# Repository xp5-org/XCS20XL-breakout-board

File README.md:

Unfinished test breakout board for the Spartan-XL XCS20XL-4TQ144C 

need to sort out the power connector and programming port layout but otherwise is mostly complete

footprint from here : https://web.archive.org/web/20240531214501/https://app.ultralibrarian.com/details/df05e96a-107f-11e9-ab3a-0a3560a4cccc/Xilinx-Inc/XCS20-4TQ144C

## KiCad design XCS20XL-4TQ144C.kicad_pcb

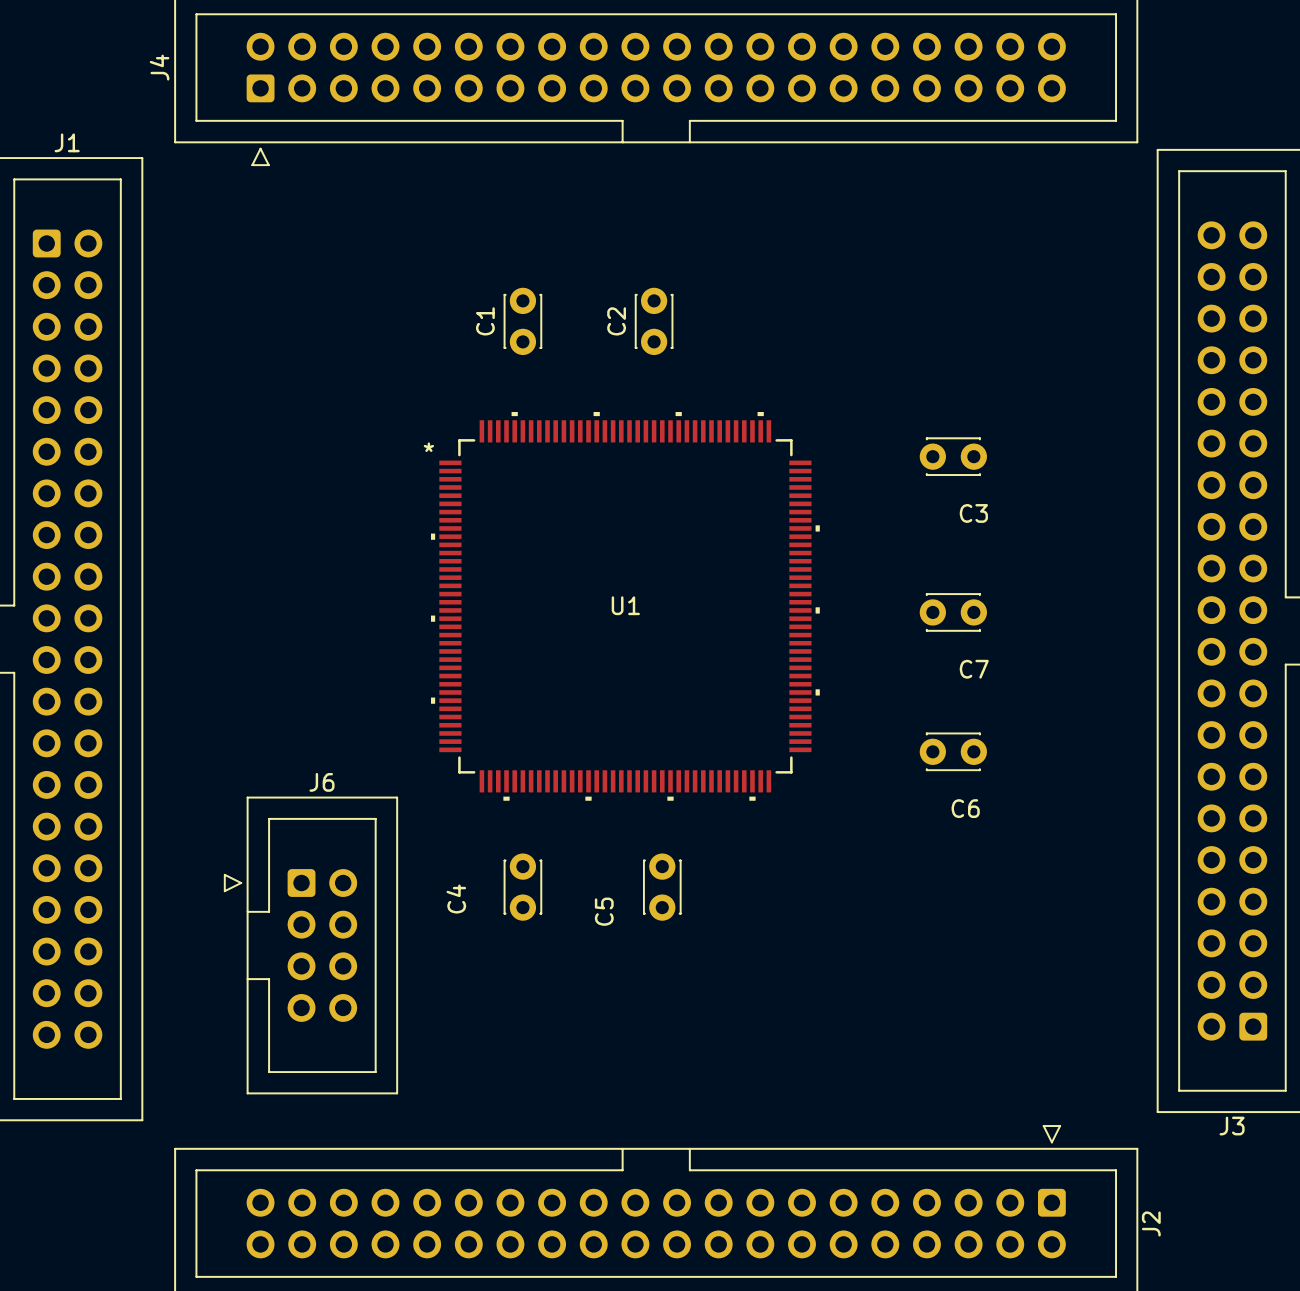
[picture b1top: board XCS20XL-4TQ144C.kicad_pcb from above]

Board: 2 copper layers, 13 parts (0 on the bottom side), 123 nets.

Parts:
C1, C2, C3, C4, C5, C6, C7: C; C_Disc_D3.0mm_W2.0mm_P2.50mm
J1, J2, J3, J4: Conn_02x20_Odd_Even; IDC-Header_2x20_P2.54mm_Vertical
J6: Conn_02x04_Odd_Even; IDC-Header_2x04_P2.54mm_Vertical
U1: XCS20-4TQ144C; 144-TQFP_XIL

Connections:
/P72_DONE: J2.1, U1.72
/P74_PROGRAM: J3.2, U1.74
/P105_DIN: J3.40, U1.105
/P106_DOUT: J3.37, U1.106
/P107_CCLK: J3.39, U1.107
GND: C1.2, C2.2, C3.2, C4.2, C5.2, C6.2, C7.2, J1.3, J1.8, J1.11, J1.16, J1.19, J1.24, J1.27, J1.32, J1.35, J2.3, J2.8, J2.11, J2.16, J2.19, J2.24, J2.27, J2.32, J2.35, J3.3, J3.8, J3.11, J3.16, J3.19, J3.24, J3.27, J3.32, J3.35, J4.3, J4.8, J4.11, J4.16, J4.19, J4.24, J4.27, J4.32, J4.35, J6.1, J6.3, J6.5, J6.7, U1.1, U1.8, U1.17, U1.27, U1.35, U1.45, U1.55, U1.64, U1.71, U1.81, U1.91, U1.100, U1.110, U1.118, U1.127, U1.137
unnamed: J1.1, U1.3
unnamed: J1.2, U1.2
unnamed: J1.4, U1.4
unnamed: J1.5, U1.5
unnamed: J1.6, U1.6
unnamed: J1.7, U1.7
unnamed: J1.9, U1.10
unnamed: J1.10, U1.9
unnamed: J1.12, U1.11
unnamed: J1.13, U1.12
unnamed: J1.14, U1.13
unnamed: J1.15, U1.14
unnamed: J1.17, U1.16
unnamed: J1.18, U1.15
unnamed: J1.20, U1.18
unnamed: J1.21, U1.19
unnamed: J1.22, U1.20
unnamed: J1.23, U1.21
unnamed: J1.25, U1.23
unnamed: J1.26, U1.22
unnamed: J1.28, U1.24
unnamed: J1.29, U1.26
unnamed: J1.30, U1.25
unnamed: J1.31, U1.29
unnamed: J1.33, U1.31
unnamed: J1.34, U1.28
unnamed: J1.36, U1.30
unnamed: J1.37, U1.34
unnamed: J1.38, U1.32
unnamed: J1.39, U1.36
unnamed: J1.40, U1.33
unnamed: J2.4, U1.70
unnamed: J2.5, U1.69
unnamed: J2.6, U1.68
unnamed: J2.7, U1.67
unnamed: J2.9, U1.65
unnamed: J2.10, U1.66
unnamed: J2.12, U1.63
unnamed: J2.13, U1.62
unnamed: J2.14, U1.61
unnamed: J2.15, U1.60
unnamed: J2.17, U1.58
unnamed: J2.18, U1.59
unnamed: J2.20, U1.57
unnamed: J2.21, U1.56
unnamed: J2.22, U1.53
unnamed: J2.23, U1.52
unnamed: J2.25, U1.50
unnamed: J2.26, U1.51
unnamed: J2.28, U1.49
unnamed: J2.29, U1.47
unnamed: J2.30, U1.48
unnamed: J2.31, U1.44
unnamed: J2.33, U1.42
unnamed: J2.34, U1.46
unnamed: J2.36, U1.43
unnamed: J2.37, U1.39
unnamed: J2.38, U1.41
unnamed: J2.39, U1.38
unnamed: J2.40, U1.40
unnamed: J3.1, U1.75
unnamed: J3.4, U1.76
unnamed: J3.5, U1.77
unnamed: J3.6, U1.78
unnamed: J3.7, U1.79
unnamed: J3.9, U1.82
unnamed: J3.10, U1.80
unnamed: J3.12, U1.83
unnamed: J3.13, U1.84
unnamed: J3.14, U1.85
unnamed: J3.15, U1.86
unnamed: J3.17, U1.88
unnamed: J3.18, U1.87
unnamed: J3.20, U1.89
unnamed: J3.22, U1.92
unnamed: J3.23, U1.93
unnamed: J3.25, U1.95
unnamed: J3.26, U1.94
unnamed: J3.28, U1.96
unnamed: J3.29, U1.98
unnamed: J3.30, U1.97
unnamed: J3.31, U1.101
unnamed: J3.33, U1.103
unnamed: J3.34, U1.99
unnamed: J3.36, U1.102
unnamed: J3.38, U1.104
unnamed: J4.1, U1.143
unnamed: J4.4, U1.142
unnamed: J4.5, U1.141
unnamed: J4.6, U1.140
unnamed: J4.7, U1.139
unnamed: J4.9, U1.136
unnamed: J4.10, U1.138
unnamed: J4.12, U1.135
unnamed: J4.13, U1.134
unnamed: J4.14, U1.133
unnamed: J4.15, U1.132
unnamed: J4.17, U1.130
unnamed: J4.18, U1.131
unnamed: J4.20, U1.129
unnamed: J4.21, U1.126
unnamed: J4.22, U1.125
unnamed: J4.23, U1.124
unnamed: J4.25, U1.122
unnamed: J4.26, U1.123
unnamed: J4.28, U1.121
unnamed: J4.29, U1.119
unnamed: J4.30, U1.120
unnamed: J4.31, U1.116
unnamed: J4.33, U1.114
unnamed: J4.34, U1.117
unnamed: J4.36, U1.115
unnamed: J4.37, U1.111
unnamed: J4.38, U1.113
unnamed: J4.39, U1.109
unnamed: J4.40, U1.112
VCC: C1.1, C2.1, C3.1, C4.1, C5.1, C6.1, C7.1, J6.2, J6.4, J6.6, J6.8, U1.37, U1.54, U1.73, U1.90, U1.108, U1.128, U1.144

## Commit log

2024-05-31 added files
    initial commit
2024-05-31 Update README.md
    added footprint url
